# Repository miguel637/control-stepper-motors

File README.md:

# remote control of scout vehicle
 The project was built for a remote control vehicle competition, using a network system, for this an ESP32 development board was used and boards made to measure for the needs, powered by a lithium battery and a camera system with a raspberry pi 3
for this proyect what i need?
*pycharm
*QtDesigner
know PyQt5
For the control, you need a Xbox one control connected by Bluetooth

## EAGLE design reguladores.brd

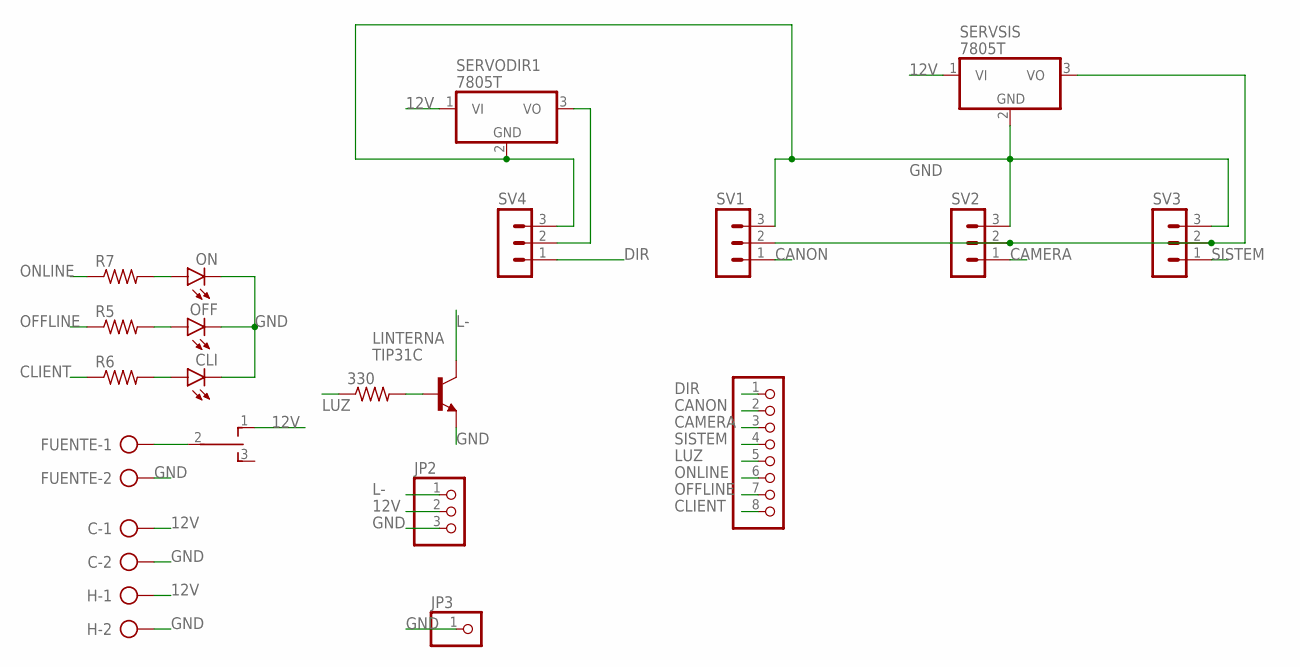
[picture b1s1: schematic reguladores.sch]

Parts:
330: R-US_0204/7; 0204/7
C: AK500/2-H
CLI: LED5MM
FUENTE: AK500/2-H
H: AK500/2-H
JP1: PINHD-1X8; 1X08
JP2: PINHD-1X3; 1X03
JP3: PINHD-1X1; 1X01
LINTERNA: TIP31C; TO220
OFF: LED5MM
ON: LED5MM
R5, R6, R7: R-US_0204/7; 0204/7
S1: TL39WO; TL3XWO
SERVODIR1: 7805T; TO220H
SERVSIS: 7805T; TO220H
SV1, SV2, SV3, SV4: MA03-1

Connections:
12V: C.1, H.1, JP2.2, S1.1 (O), SERVODIR1.1 (VI), SERVSIS.1 (VI)
CAMERA: JP1.3, SV2.1
CANON: JP1.2, SV1.1
CLIENT: JP1.8, R6.1
DIR: JP1.1, SV4.1
GND: C.2, CLI.K (C), FUENTE.2, H.2, JP2.3, JP3.1, LINTERNA.3 (E), OFF.K (C), ON.K (C), SERVODIR1.2 (GND), SERVSIS.2 (GND), SV1.3, SV2.3, SV3.3, SV4.3
L-: JP2.1, LINTERNA.2 (C)
LUZ: 330.1, JP1.5
unnamed: SERVSIS.3 (VO), SV1.2, SV2.2, SV3.2
unnamed: FUENTE.1, S1.2
unnamed: SERVODIR1.3 (VO), SV4.2
unnamed: 330.2, LINTERNA.1 (B)
unnamed: ON.A, R7.2
unnamed: OFF.A, R5.2
unnamed: CLI.A, R6.2
OFFLINE: JP1.7, R5.1
ONLINE: JP1.6, R7.1
SISTEM: JP1.4, SV3.1

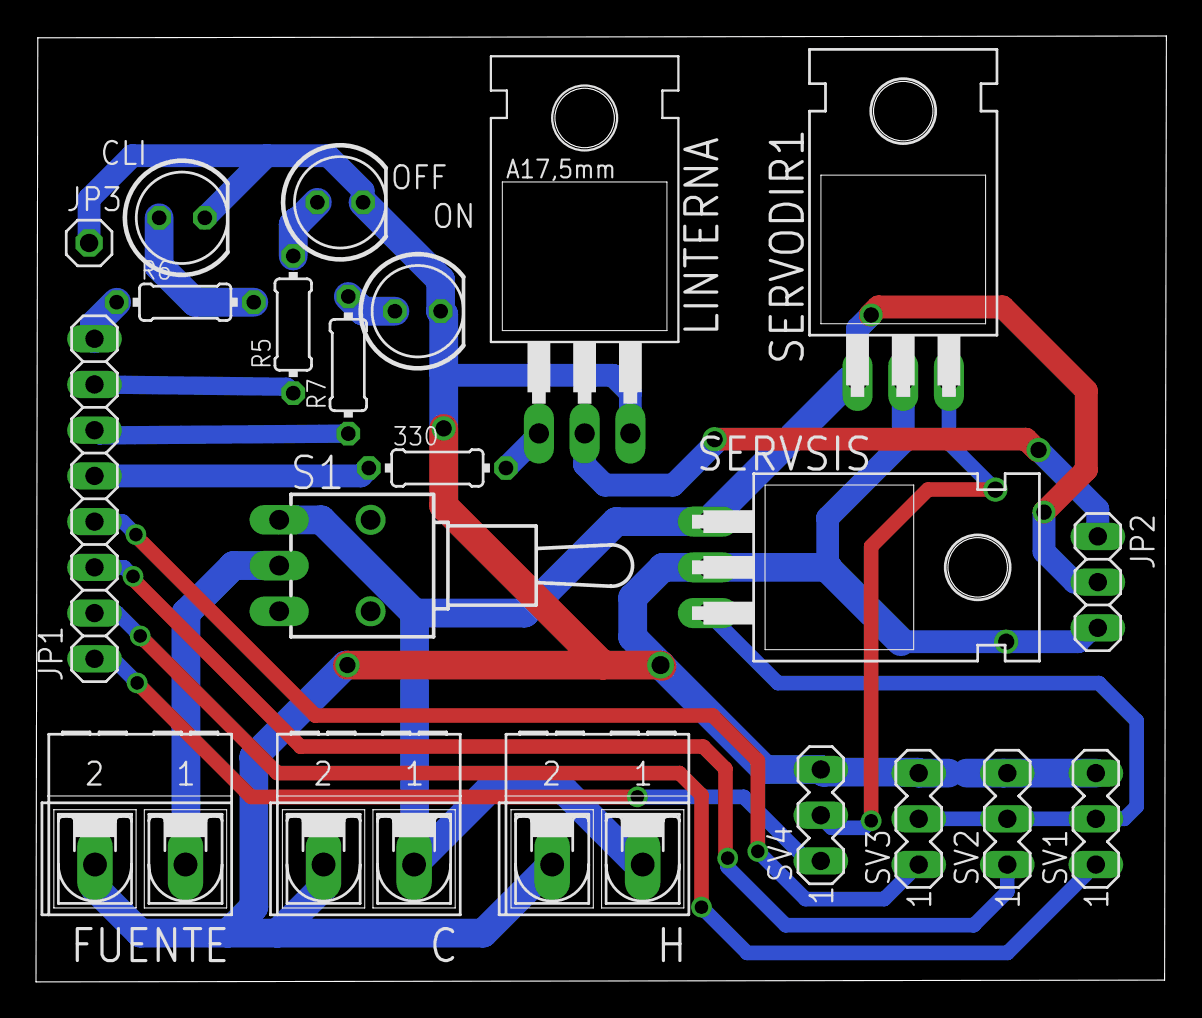
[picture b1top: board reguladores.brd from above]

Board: 2 copper layers, 62.8 x 52.5 mm, 21 parts (0 on the bottom side), 18 nets.

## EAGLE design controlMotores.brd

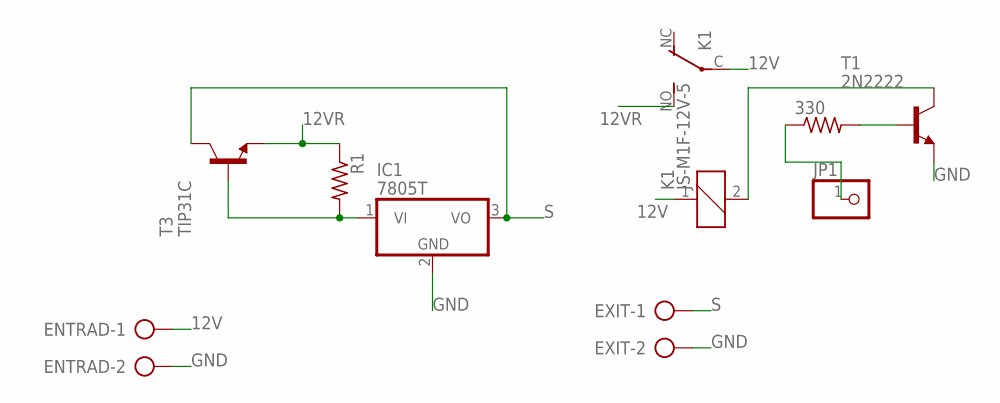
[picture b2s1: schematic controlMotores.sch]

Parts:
330: R-US_0204/7; 0204/7
ENTRAD: AK500/2-H
EXIT: AK500/2-H
IC1: 7805T; TO220H
JP1: PINHD-1X1; 1X01
K1: JS-M1F-12V-5; JS-M
R1: R-US_0207/12; 0207/12
T1: 2N2222; TO18
T3: TIP31C; TO220

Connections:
12V: ENTRAD.1, K1.1, K1.C
12VR: K1.NO (S), R1.1, T3.3 (E)
GND: ENTRAD.2, EXIT.2, IC1.2 (GND), T1.1 (E)
unnamed: 330.1, JP1.1
unnamed: 330.2, T1.2 (B)
unnamed: K1.2, T1.3 (C)
unnamed: IC1.1 (VI), R1.2, T3.1 (B)
S: EXIT.1, IC1.3 (VO), T3.2 (C)

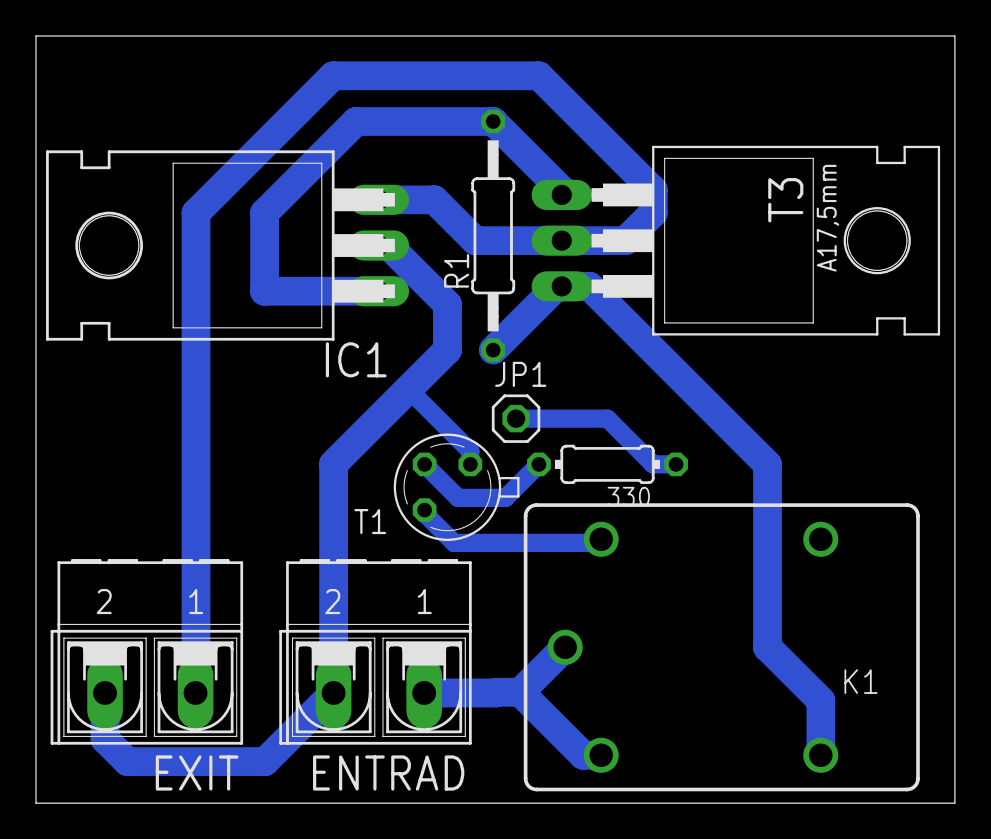
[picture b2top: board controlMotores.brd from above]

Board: 2 copper layers, 51.0 x 42.6 mm, 9 parts (0 on the bottom side), 8 nets.
